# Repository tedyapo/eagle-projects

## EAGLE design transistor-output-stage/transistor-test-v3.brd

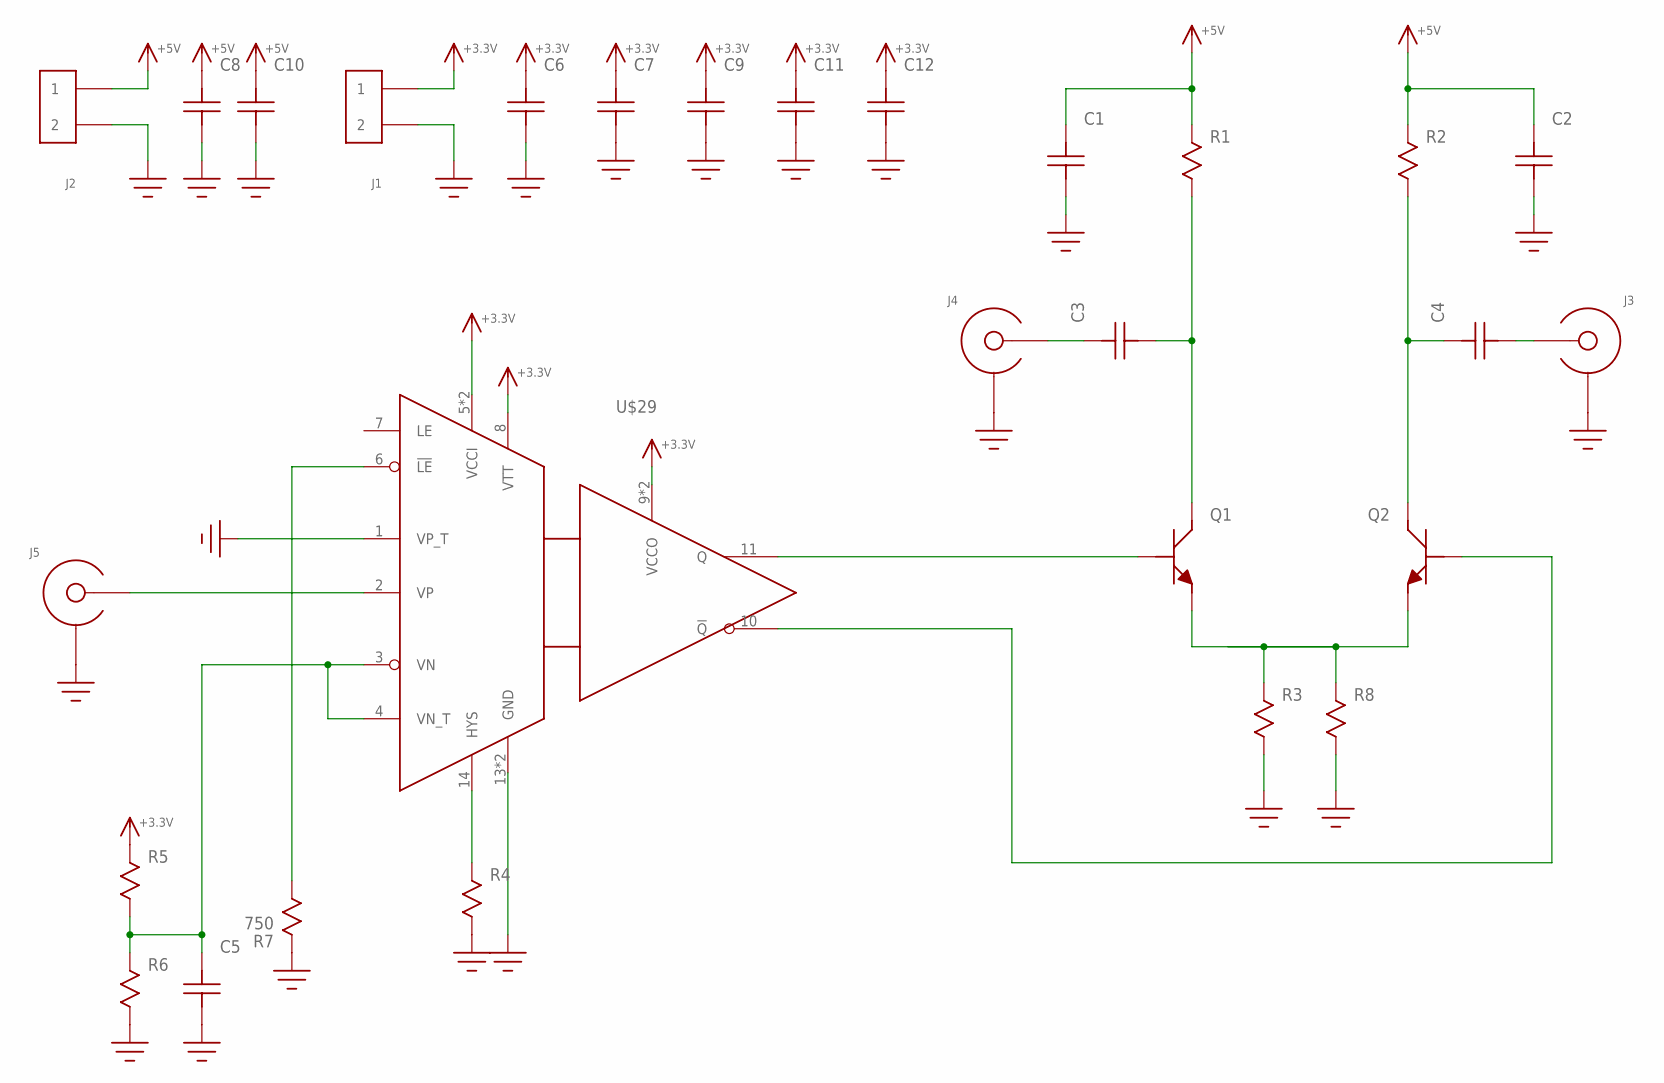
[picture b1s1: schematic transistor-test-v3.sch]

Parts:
C1, C2, C3, C4, C5, C7, C9, C11, C12: C0603
C6, C8, C10: C1206; 1206
J1, J2: HEADER_2PIN
J3, J4, J5: SMA-EDGE-LAUNCH4L_4030_TAPER; SMA_EDGE_LAUNCH_4L_4030_TAPER
Q1, Q2: MCH4020; SOT343
R1, R2, R3, R4, R5, R6, R8: R0603
R7: 750; R0603
U$29: ADCMP572; TQFN16-EP

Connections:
+3.3V: C6.P$2, C7.P$2, C9.P$2, C11.P$2, C12.P$2, J1.1, R5.P$1, U$29.5 (VCCI), U$29.8 (VTT), U$29.9 (VCCO), U$29.12 (VCCO), U$29.16 (VCCI)
+5V: C1.P$2, C2.P$2, C8.P$2, C10.P$2, J2.1, R1.P$1, R2.P$1
GND: C1.P$1, C2.P$1, C5.P$1, C6.P$1, C7.P$1, C8.P$1, C9.P$1, C10.P$1, C11.P$1, C12.P$1, J1.2, J2.2, J3.BOTTOM_GND (SHIELD), J3.GND@1 (SHIELD), J3.GND@2 (SHIELD), J3.GND@3 (SHIELD), J3.GND@4 (SHIELD), J3.GND@5 (SHIELD), J3.GND@6 (SHIELD), J3.GND@7 (SHIELD), J3.GND@8 (SHIELD), J3.GND@14 (SHIELD), J3.GND@15 (SHIELD), J3.GND@16 (SHIELD), J3.GND@17 (SHIELD), J3.GND_PAD1 (SHIELD), J3.GND_PAD2 (SHIELD), J3.P$1 (SHIELD), J3.P$2 (SHIELD), J4.BOTTOM_GND (SHIELD), J4.GND@1 (SHIELD), J4.GND@2 (SHIELD), J4.GND@3 (SHIELD), J4.GND@4 (SHIELD), J4.GND@5 (SHIELD), J4.GND@6 (SHIELD), J4.GND@7 (SHIELD), J4.GND@8 (SHIELD), J4.GND@14 (SHIELD), J4.GND@15 (SHIELD), J4.GND@16 (SHIELD), J4.GND@17 (SHIELD), J4.GND_PAD1 (SHIELD), J4.GND_PAD2 (SHIELD), J4.P$1 (SHIELD), J4.P$2 (SHIELD), J5.BOTTOM_GND (SHIELD), J5.GND@1 (SHIELD), J5.GND@2 (SHIELD), J5.GND@3 (SHIELD), J5.GND@4 (SHIELD), J5.GND@5 (SHIELD), J5.GND@6 (SHIELD), J5.GND@7 (SHIELD), J5.GND@8 (SHIELD), J5.GND@14 (SHIELD), J5.GND@15 (SHIELD), J5.GND@16 (SHIELD), J5.GND@17 (SHIELD), J5.GND_PAD1 (SHIELD), J5.GND_PAD2 (SHIELD), J5.P$1 (SHIELD), J5.P$2 (SHIELD), R3.P$2, R4.P$2, R6.P$2, R7.P$1, R8.P$2, U$29.1 (VP_T), U$29.13 (GND), U$29.15 (GND)
unnamed: Q1.2 (E), Q1.4 (E), Q2.2 (E), Q2.4 (E), R3.P$1, R8.P$1
unnamed: R4.P$1, U$29.14 (HYS)
unnamed: Q2.3 (B), U$29.10 (!Q!)
unnamed: C3.P$2, J4.CENTER@1 (CENTER)
unnamed: C4.P$1, J3.CENTER@1 (CENTER)
unnamed: C5.P$2, R5.P$2, R6.P$1, U$29.3 (VN), U$29.4 (VN_T)
unnamed: R7.P$2, U$29.6 (!LE!)
unnamed: J5.CENTER@1 (CENTER), U$29.2 (VP)
unnamed: C3.P$1, Q1.1 (C), R1.P$2
unnamed: C4.P$2, Q2.1 (C), R2.P$2
unnamed: Q1.3 (B), U$29.11 (Q)

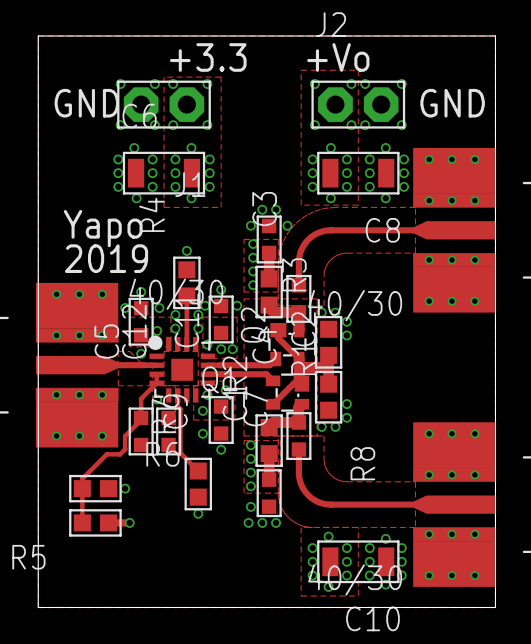
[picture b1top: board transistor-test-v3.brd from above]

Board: 4 copper layers, 25.4 x 31.8 mm, 28 parts (0 on the bottom side), 14 nets.

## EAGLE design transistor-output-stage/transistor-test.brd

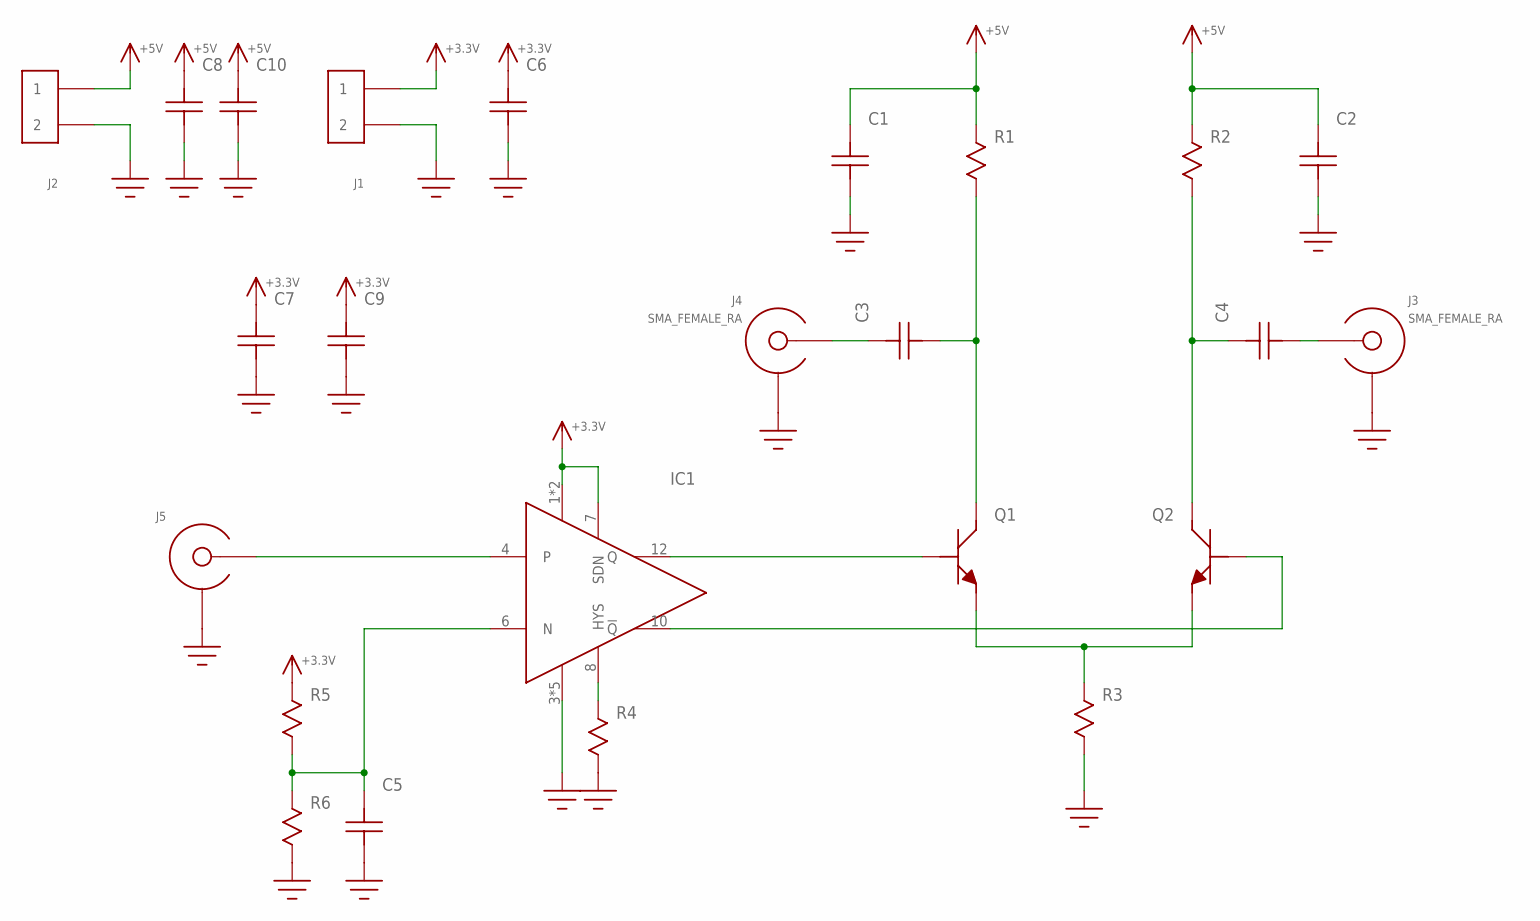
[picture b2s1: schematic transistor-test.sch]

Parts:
C1, C2, C3, C4, C5, C7, C9: C0603
C6, C8, C10: C1206; 1206
IC1: ADCMP607; QFN12-3X3
J1, J2: HEADER_2PIN
J3, J4: SMA_FEMALE_RA; SMA_RA_PCB
J5: SMA_END_LAUNCH2L; SMA_EDGE_LAUNCH_2L
Q1, Q2: MMBTH10; SOT-23
R1, R2, R3, R4, R5, R6: R0603

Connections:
+3.3V: C6.P$2, C7.P$2, C9.P$2, IC1.1 (VCC), IC1.2 (VCC), IC1.7 (SDN), J1.1, R5.P$1
+5V: C1.P$2, C2.P$2, C8.P$2, C10.P$2, J2.1, R1.P$1, R2.P$1
GND: C1.P$1, C2.P$1, C5.P$1, C6.P$1, C7.P$1, C8.P$1, C9.P$1, C10.P$1, IC1.3 (VEE), IC1.5 (VEE), IC1.9 (VEE), IC1.11 (VEE), IC1.EP (VEE), J1.2, J2.2, J3.SHIELD@1 (SHIELD), J3.SHIELD@2 (SHIELD), J3.SHIELD@3 (SHIELD), J3.SHIELD@4 (SHIELD), J4.SHIELD@1 (SHIELD), J4.SHIELD@2 (SHIELD), J4.SHIELD@3 (SHIELD), J4.SHIELD@4 (SHIELD), J5.BOTTOM_GND (SHIELD), J5.GND@1 (SHIELD), J5.GND@2 (SHIELD), J5.GND@3 (SHIELD), J5.GND@4 (SHIELD), J5.GND@5 (SHIELD), J5.GND@6 (SHIELD), J5.GND@7 (SHIELD), J5.GND@8 (SHIELD), J5.GND@11 (SHIELD), J5.GND@12 (SHIELD), J5.GND@14 (SHIELD), J5.GND@15 (SHIELD), J5.GND@16 (SHIELD), J5.GND@17 (SHIELD), J5.GND_PAD1 (SHIELD), J5.GND_PAD2 (SHIELD), R3.P$2, R4.P$2, R6.P$2
unnamed: C3.P$1, Q1.3 (C), R1.P$2
unnamed: C4.P$2, Q2.3 (C), R2.P$2
unnamed: Q1.2 (E), Q2.2 (E), R3.P$1
unnamed: IC1.12 (Q), Q1.1 (B)
unnamed: IC1.10 (!Q!), Q2.1 (B)
unnamed: C3.P$2, J4.CENTER
unnamed: C4.P$1, J3.CENTER
unnamed: C5.P$2, IC1.6 (N), R5.P$2, R6.P$1
unnamed: IC1.8 (HYS), R4.P$1
unnamed: IC1.4, J5.CENTER@1 (CENTER)

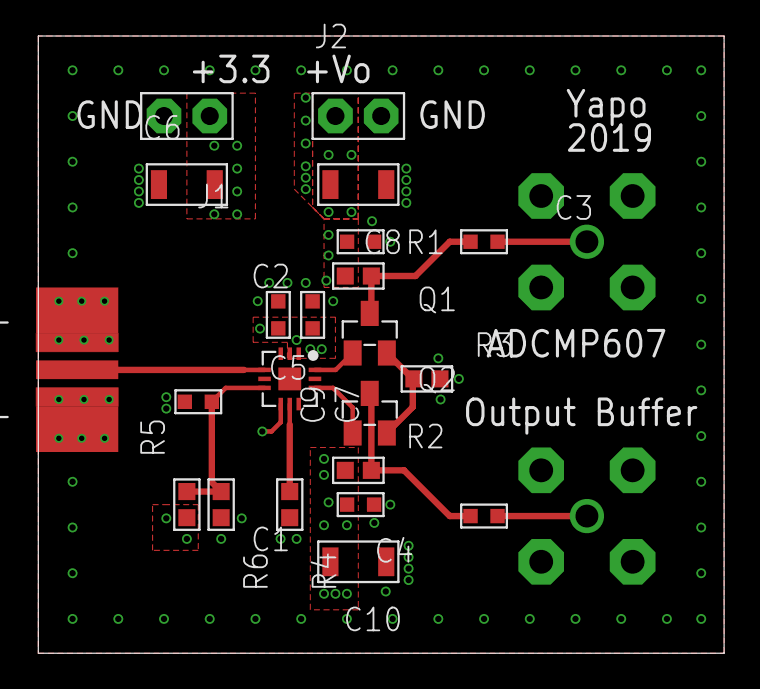
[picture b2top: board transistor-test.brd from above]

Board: 4 copper layers, 38.1 x 34.3 mm, 24 parts (0 on the bottom side), 13 nets.

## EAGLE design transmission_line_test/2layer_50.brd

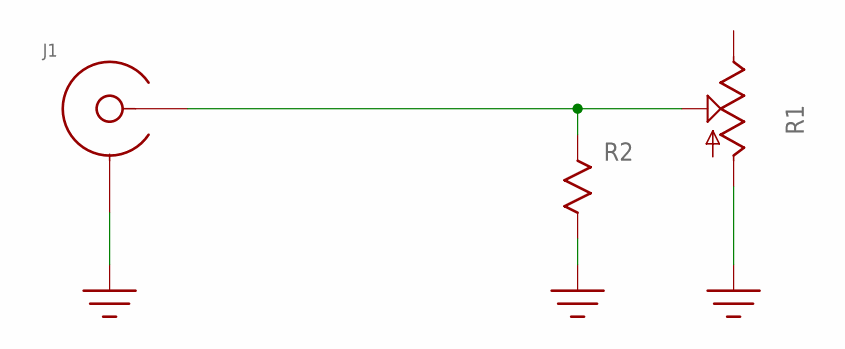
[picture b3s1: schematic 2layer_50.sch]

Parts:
J1: EDGE_LAUNCH_JACKNARROW; EDGE_LAUNCH_RF_CON_NARROW
R1: TRIM_US-SP19L; SP19L
R2: R0603

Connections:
GND: J1.GND@1 (SHIELD), J1.GND@2 (SHIELD), J1.GND@3 (SHIELD), J1.GND@4 (SHIELD), J1.GND@5 (SHIELD), J1.GND@6 (SHIELD), J1.SHIELD@1 (SHIELD), J1.SHIELD@2 (SHIELD), R1.A, R2.P$2
unnamed: J1.CENTER, R1.S, R2.P$1

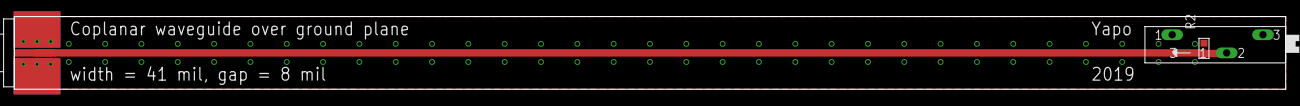
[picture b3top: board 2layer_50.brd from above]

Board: 2 copper layers, 177.8 x 10.2 mm, 3 parts (0 on the bottom side), 2 nets.

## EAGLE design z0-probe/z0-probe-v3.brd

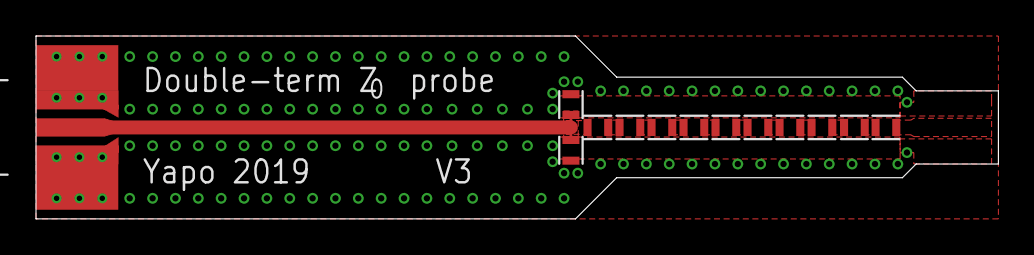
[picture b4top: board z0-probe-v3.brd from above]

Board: 2 copper layers, 53.5 x 10.2 mm, 13 parts (0 on the bottom side), 11 nets.

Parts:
J1: SMA_EDGE_LAUNCH_2L_4020_TAPER_FIXED
R1, R2, R3, R4, R5, R6, R7, R8, R9, R10, R11, R12: 0603_TIGHT

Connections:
GND: J1.BOTTOM_GND, J1.GND@1, J1.GND@2, J1.GND@3, J1.GND@4, J1.GND@5, J1.GND@6, J1.GND@7, J1.GND@8, J1.GND@14, J1.GND@15, J1.GND@16, J1.GND@17, J1.GND_PAD1, J1.GND_PAD2, J1.P$1, J1.P$2, R10.P$2, R11.P$1
unnamed: R2.P$2, R3.P$1
unnamed: R3.P$2, R4.P$1
unnamed: R4.P$2, R5.P$1
unnamed: R5.P$2, R6.P$1
unnamed: R6.P$2, R7.P$1
unnamed: R7.P$2, R8.P$1
unnamed: R8.P$2, R9.P$1
unnamed: J1.CENTER@1, J1.P$3, R9.P$2, R10.P$1, R11.P$2
unnamed: R1.P$2, R12.P$1
unnamed: R2.P$1, R12.P$2
